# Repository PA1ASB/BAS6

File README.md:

# BAS6 - Remote controlled receive antenna switch for 6 beverage antennas

This project describes a 6-way receive antenna switch I built for a fellow radio amateur that allows to select one of six beverage wire antennas remotely and producing as little as possible noise around the connection to his receive amplifier. Using bi-stable relays makes it possible to completely disconnect power to the relays once an antenna has been selected. Switching is controlled by a small circuit, built in a tiny aluminium extrusion desktop enclosure, using two UP/DOWN tactile switches. Bi-colour LED’s on the from panel indicate the currently connected antenna and, when using the selection buttons, the next antenna to be switched on. Connection between the control station in the shack and the actual relay box requires 4 wires; using cheap UTP/FTP is therefore possible. The circuit should work over distances in excess of 200 meters as communication between the stations is done through two current loops (receive and transmit).

Control unit and relay box communicate “digitally” by sending some pulses to and fro, the number of which determine what the relaybox should actually do. After executing a command, the circuit measures which relay is actually switched on / off and reports this back to the control unit again as a series of pulses. If for whatever reason the reported switch state differs from what has been commanded, an error is indicated so that  the user knows there’s something wrong. This will prevent unnecessary walks from the shack to the antenna connections: what is  indicated on the control unit is the actual state.

The antennas are connected to the switch on the PVC junction box. I have made quite some effort in making the box and connections that are located outside of the box as watertight as possible but I guess that it is still advisable to make some additional protection to prevent direct exposure to the environment.

You can find the schematics of both units both as PDF and KiCAD v10 files as well as the C sources. I have also included BOM files for the PCB’s. There’s some additional hardware required such as stainless steel hardware for the antenna connections and switches to control the relays; these are not mentioned in these files. I have built the software in MPLAB IDE with the XC8 1.33 compiler. The C source should also compile in the newer MPLAB X IDE with the newer compiler versions but I believe that there are some minor syntax changes between the old and new versions which obviously need to be resolved. Google will be your friend for that, I guess.

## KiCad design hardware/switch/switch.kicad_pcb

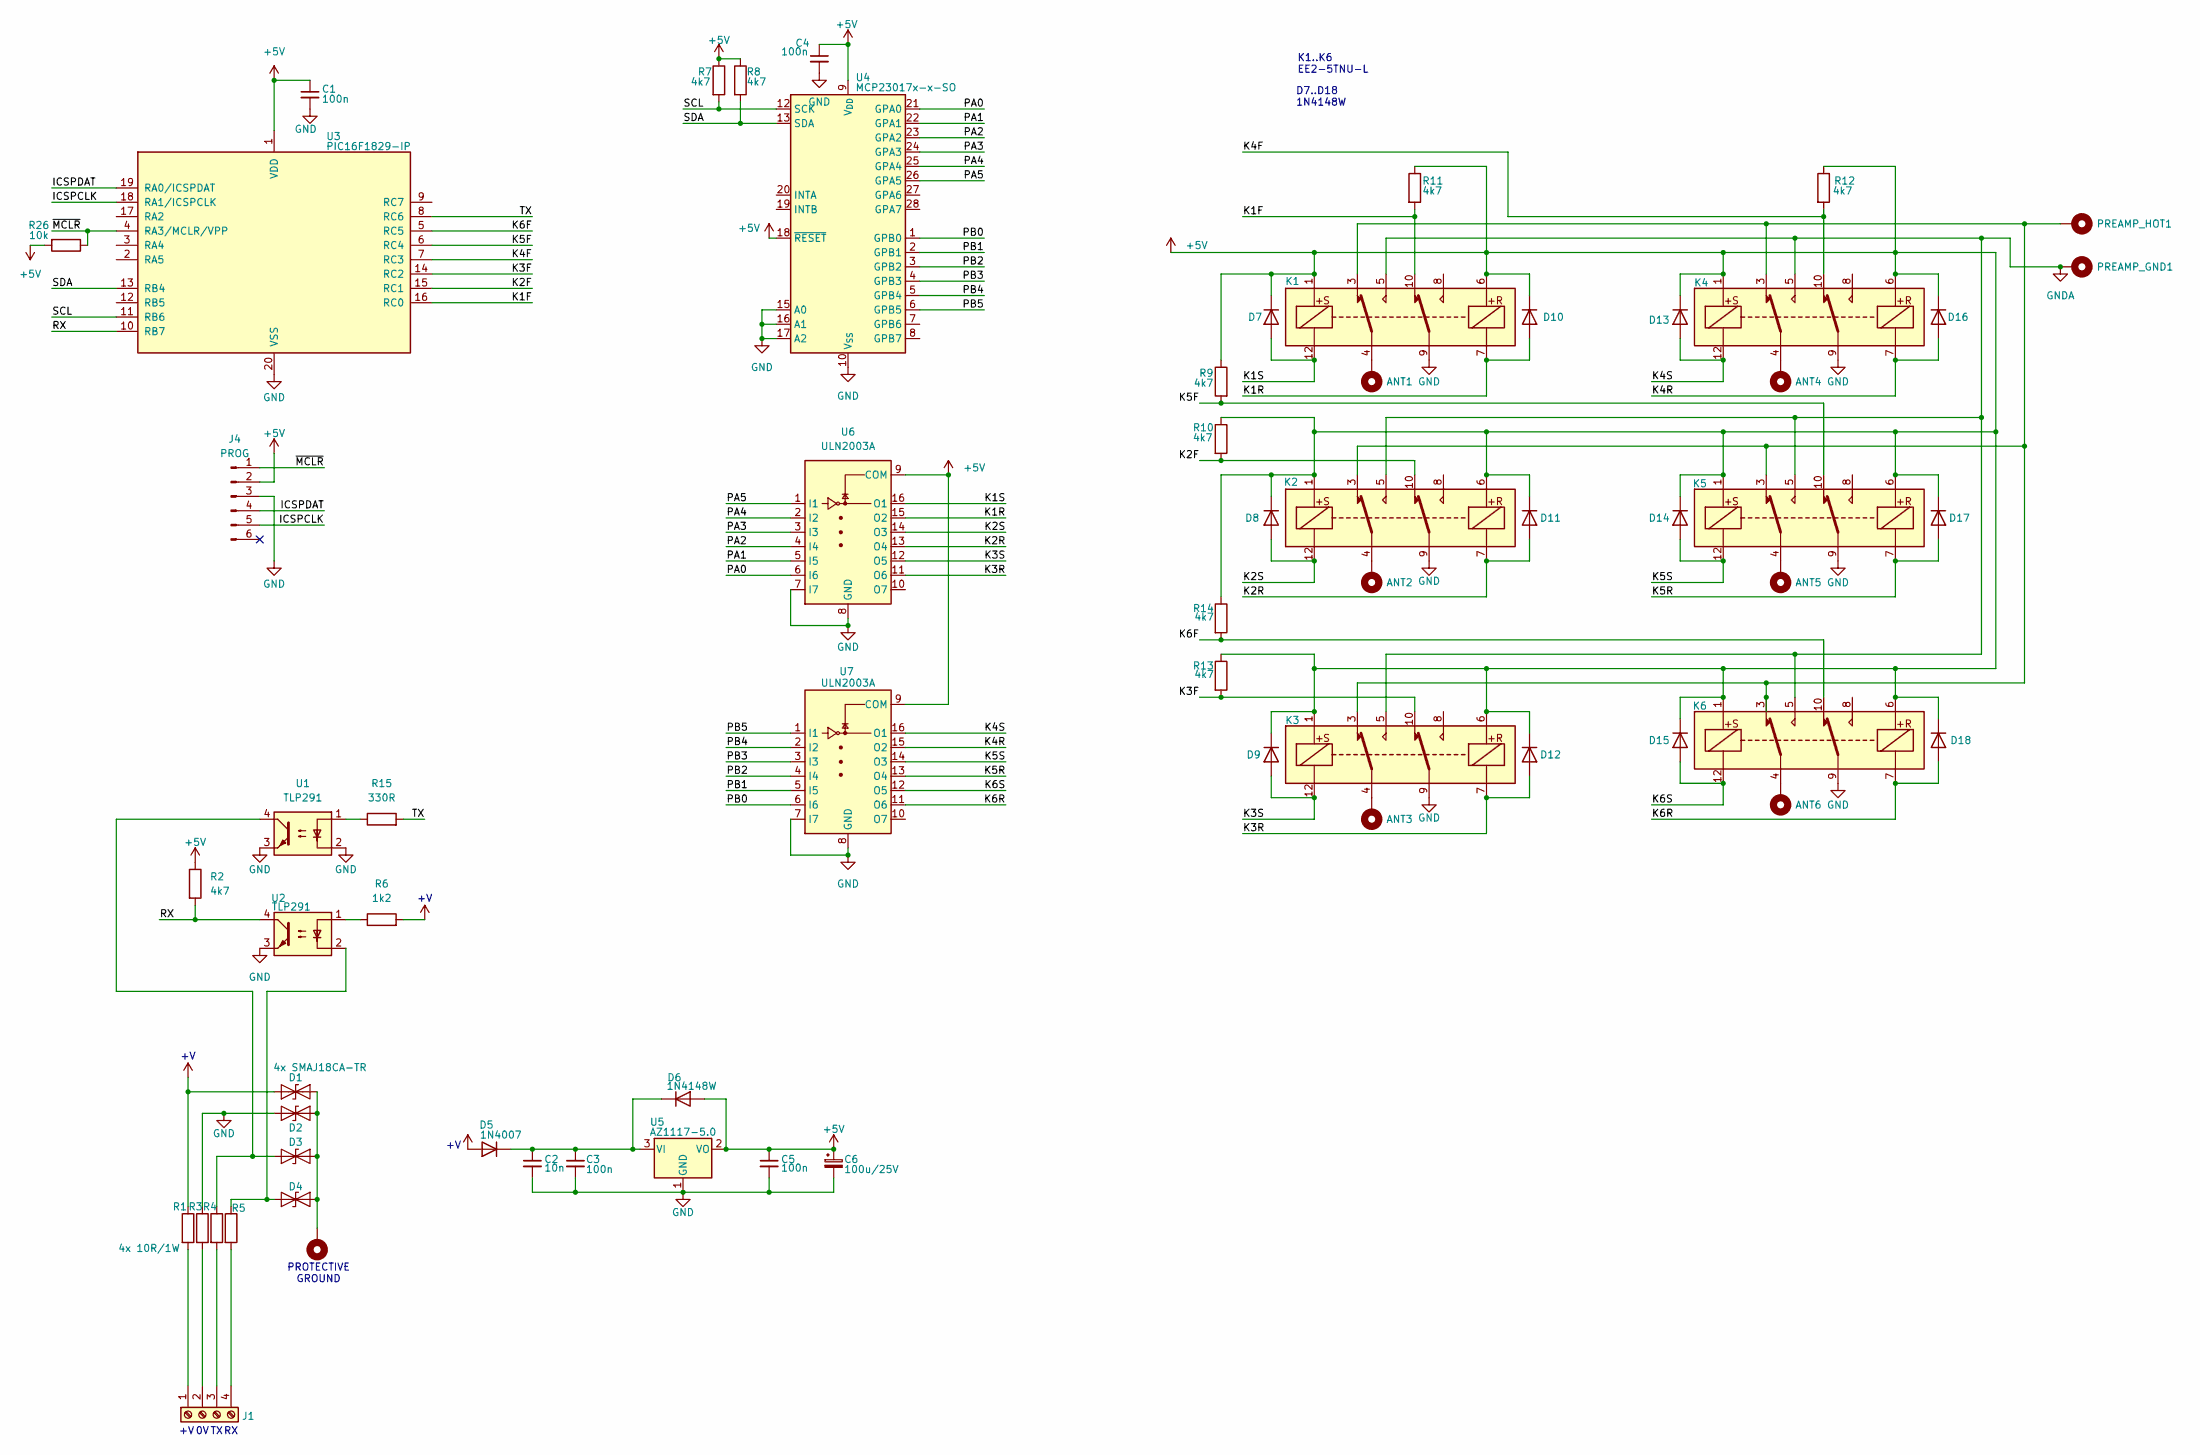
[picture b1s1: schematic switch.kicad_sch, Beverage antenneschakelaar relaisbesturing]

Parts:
ANT1, ANT2, ANT3, ANT4, ANT5, ANT6: MountingHole_Pad; MountingHole_4.3mm_M4_Pad_TopBottom
C1, C3, C4, C5: 100n; C_0805_2012Metric_Pad1.18x1.45mm_HandSolder
C2: 10n; C_0805_2012Metric_Pad1.18x1.45mm_HandSolder
C6: 100u/25V; CP_Elec_10x10
D1, D2, D3: SMAJ18CA-TR; D_SMA
D4: 4x SMAJ18CA-TR; D_SMA
D5: 1N4007; D_DO-41_SOD81_P10.16mm_Horizontal
D6, D7, D8, D9, D10, D11, D12, D13, D14, D15, D16, D17, D18: 1N4148W; D_SOD-123
GROUND1: MountingHole_Pad; MountingHole_5.3mm_M5_DIN965_Pad_TopBottom
J1: Screw_Terminal_01x04; TerminalBlock_Phoenix_MPT-0,5-4-2.54_1x04_P2.54mm_Horizontal
J4: PROG; PinHeader_1x06_P2.54mm_Vertical
K1, K2, K3, K4, K5, K6: EE2-5TNU-L; Relay_DPDT_Kemet_EE2_NU_DoubleCoil
PREAMP_GND1: MountingHole_Pad; MountingHole_4.3mm_M4_Pad_TopBottom
PREAMP_HOT1: MountingHole_Pad; MountingHole_4.3mm_M4_Pad_TopBottom
R1, R4, R5: 10R/1W; R_1206_3216Metric_Pad1.30x1.75mm_HandSolder
R2, R7, R8, R9, R10, R11, R12, R13, R14: 4k7; R_0805_2012Metric_Pad1.20x1.40mm_HandSolder
R3: 4x 10R/1W; R_1206_3216Metric_Pad1.30x1.75mm_HandSolder
R6: 1k2; R_0805_2012Metric_Pad1.20x1.40mm_HandSolder
R15: 330R; R_0805_2012Metric_Pad1.20x1.40mm_HandSolder
R26: 10k; R_0805_2012Metric_Pad1.20x1.40mm_HandSolder
U1, U2: TLP291; SOIC-4_4.55x2.6mm_P1.27mm
U3: PIC16F1829-IP; SOIC-20W_7.5x12.8mm_P1.27mm
U4: MCP23017x-x-SO; SOIC-28W_7.5x17.9mm_P1.27mm
U5: AZ1117-5.0; SOT-223-3_TabPin2
U6, U7: ULN2003A; SOIC-16_3.9x9.9mm_P1.27mm

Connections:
+5V: C1.1, C4.1, C5.1, C6.1, D6.2 (A), D7.1 (K), D8.1 (K), D9.1 (K), D10.1 (K), D11.1 (K), D12.1 (K), D13.1 (K), D14.1 (K), D15.1 (K), D16.1 (K), D17.1 (K), D18.1 (K), J4.2, K1.1, K1.6, K2.1, K2.6, K3.1, K3.6, K4.1, K4.6, K5.1, K5.6, K6.1, K6.6, R2.1, R7.1, R8.1, R9.1, R10.1, R11.1, R12.1, R13.1, R14.1, R26.2, U3.1 (VDD), U4.9 (V_{DD}), U4.18 (~RESET), U5.2 (VO), U6.9 (COM), U7.9 (COM)
+12V: D1.1 (A1), D5.2 (A), R1.1, R6.2
/ICSPCLK: J4.5, U3.18 (RA1/ICSPCLK)
/ICSPDAT: J4.4, U3.19 (RA0/ICSPDAT)
/K1F: K1.10, R11.2, U3.16 (RC0)
/K1R: D10.2 (A), K1.7, U6.15 (O2)
/K1S: D7.2 (A), K1.12, U6.16 (O1)
/K2F: K2.10, R10.2, U3.15 (RC1)
/K2R: D11.2 (A), K2.7, U6.13 (O4)
/K2S: D8.2 (A), K2.12, U6.14 (O3)
/K3F: K3.10, R13.2, U3.14 (RC2)
/K3R: D12.2 (A), K3.7, U6.11 (O6)
/K3S: D9.2 (A), K3.12, U6.12 (O5)
/K4F: K4.10, R12.2, U3.7 (RC3)
/K4R: D16.2 (A), K4.7, U7.15 (O2)
/K4S: D13.2 (A), K4.12, U7.16 (O1)
/K5F: K5.10, R9.2, U3.6 (RC4)
/K5R: D17.2 (A), K5.7, U7.13 (O4)
/K5S: D14.2 (A), K5.12, U7.14 (O3)
/K6F: K6.10, R14.2, U3.5 (RC5)
/K6R: D18.2 (A), K6.7, U7.11 (O6)
/K6S: D15.2 (A), K6.12, U7.12 (O5)
/PA0: U4.21 (GPA0), U6.6 (I6)
/PA1: U4.22 (GPA1), U6.5 (I5)
/PA2: U4.23 (GPA2), U6.4 (I4)
/PA3: U4.24 (GPA3), U6.3 (I3)
/PA4: U4.25 (GPA4), U6.2 (I2)
/PA5: U4.26 (GPA5), U6.1 (I1)
/PB0: U4.1 (GPB0), U7.6 (I6)
/PB1: U4.2 (GPB1), U7.5 (I5)
/PB2: U4.3 (GPB2), U7.4 (I4)
/PB3: U4.4 (GPB3), U7.3 (I3)
/PB4: U4.5 (GPB4), U7.2 (I2)
/PB5: U4.6 (GPB5), U7.1 (I1)
/RX: R2.2, U2.4, U3.10 (RB7)
/SCL: R7.2, U3.11 (RB6), U4.12 (SCK)
/SDA: R8.2, U3.13 (RB4), U4.13 (SDA)
/TX: R15.2, U3.8 (RC6)
/~MCLR: J4.1, R26.1, U3.4 (RA3/MCLR/VPP)
GND: C1.2, C2.2, C3.2, C4.2, C5.2, C6.2, D2.1 (A1), J4.3, K1.9, K2.9, K3.9, K4.9, K5.9, K6.9, R3.1, U1.2, U1.3, U2.3, U3.20 (VSS), U4.10 (V_{SS}), U4.15 (A0), U4.16 (A1), U4.17 (A2), U5.1 (GND), U6.7 (I7), U6.8 (GND), U7.7 (I7), U7.8 (GND)
GNDA: K1.5, K2.5, K3.5, K4.5, K5.5, K6.5, PREAMP_GND1.1 (1_1)
unnamed: ANT1.1 (1_1), K1.4
unnamed: ANT2.1 (1_1), K2.4
unnamed: ANT3.1 (1_1), K3.4
unnamed: ANT4.1 (1_1), K4.4
unnamed: ANT5.1 (1_1), K5.4
unnamed: ANT6.1 (1_1), K6.4
unnamed: D1.2 (A2), D2.2 (A2), D3.2 (A2), D4.2 (A2), GROUND1.1 (1_1)
unnamed: D3.1 (A1), R4.1, U1.4
unnamed: D4.1 (A1), R5.1, U2.2
unnamed: C2.1, C3.1, D5.1 (K), D6.1 (K), U5.3 (VI)
unnamed: J1.1, R1.2
unnamed: J1.2, R3.2
unnamed: J1.3, R4.2
unnamed: J1.4, R5.2
unnamed: K1.3, K2.3, K3.3, K4.3, K5.3, K6.3, PREAMP_HOT1.1 (1_1)
unnamed: R6.1, U2.1
unnamed: R15.1, U1.1

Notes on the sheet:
K1..K6 EE2-5TNU-L
D7..D18 1N4148W
PROTECTIVE GROUND

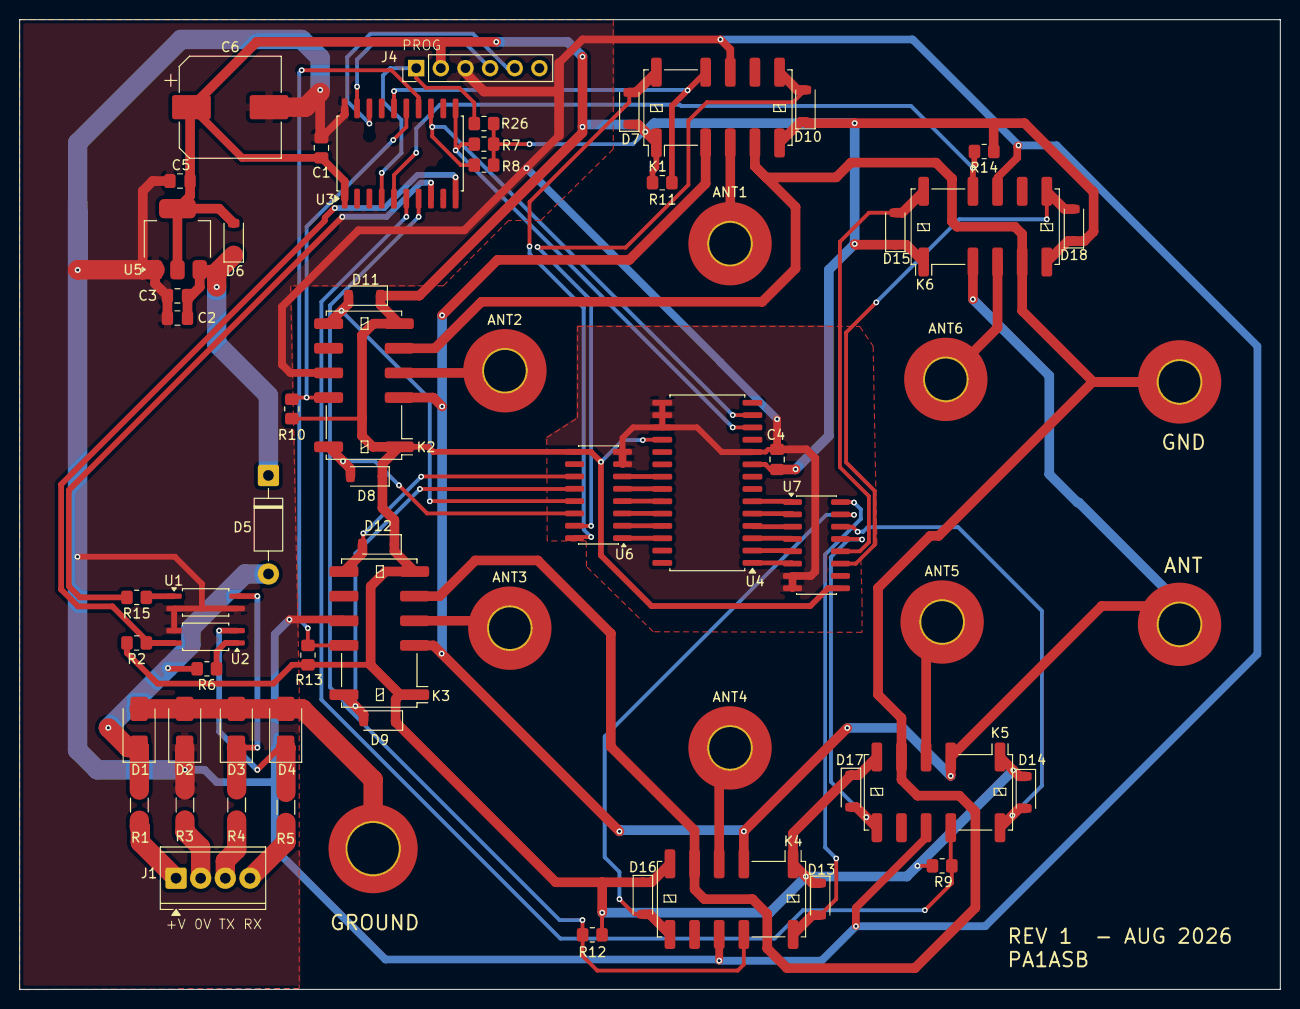
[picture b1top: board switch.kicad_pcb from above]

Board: 2 copper layers, 130.0 x 100.0 mm, 64 parts (0 on the bottom side), 58 nets.

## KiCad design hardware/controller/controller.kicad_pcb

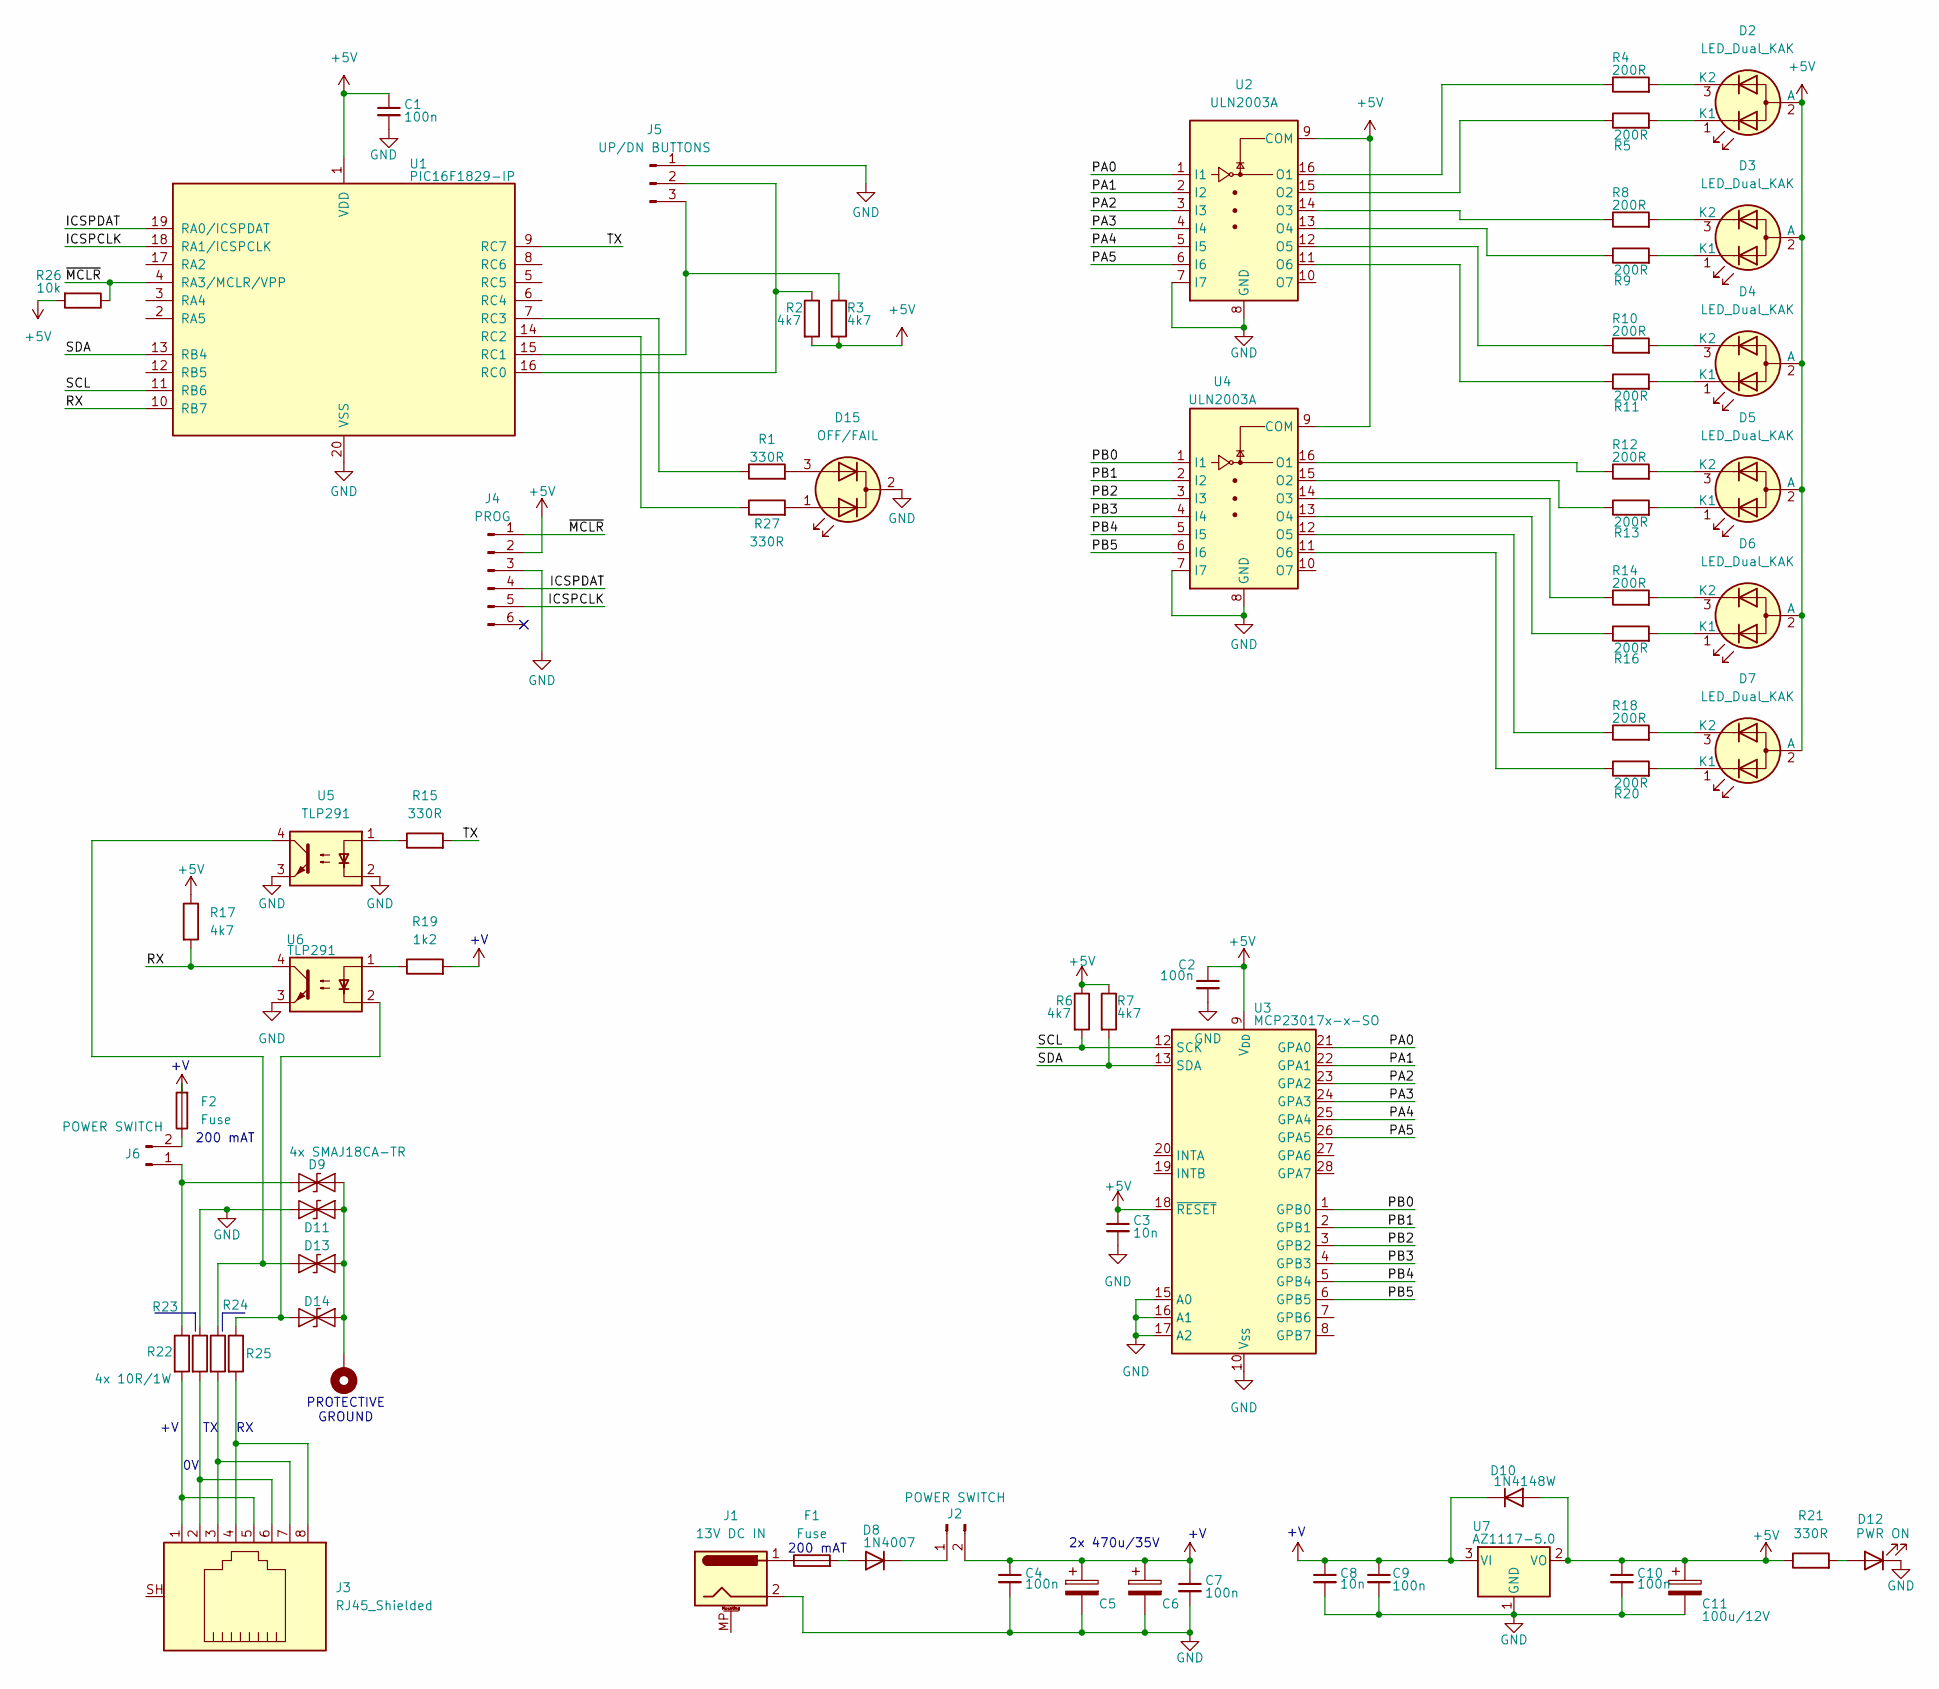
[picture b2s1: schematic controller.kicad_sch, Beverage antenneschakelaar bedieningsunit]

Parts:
C1, C2, C4, C7, C9, C10: 100n; C_0805_2012Metric_Pad1.18x1.45mm_HandSolder
C3, C8: 10n; C_0805_2012Metric_Pad1.18x1.45mm_HandSolder
C5, C6: 470u/35V; CP_Radial_D8.0mm_P3.50mm
C11: 100u/12V; CP_Radial_D8.0mm_P3.50mm
D2, D3, D4, D5, D6, D7: LED_Dual_KAK; LED_D5.0mm-3_Horizontal_O3.81mm_Z3.0mm
D8: 1N4007; D_DO-41_SOD81_P10.16mm_Horizontal
D9, D11, D13: SMAJ18CA-TR; D_SMA
D10: 1N4148W; D_SOD-123
D12: PWR ON; LED_D5.0mm_Horizontal_O6.35mm_Z15.0mm
D14: 4x SMAJ18CA-TR; D_SMA
D15: OFF/FAIL; LED_D5.0mm-3_Horizontal_O3.81mm_Z3.0mm
F1, F2: Fuse; Fuseholder_Cylinder-5x20mm_Stelvio-Kontek_PTF78_Horizontal_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
GROUND1: MountingHole_Pad; MountingHole_2.2mm_M2_DIN965_Pad_TopBottom
J1: 13V DC IN; BarrelJack_GCT_DCJ200-10-A_Horizontal
J2, J6: POWER SWITCH; PinHeader_1x02_P2.54mm_Vertical
J3: RJ45_Shielded; RJ45_Amphenol_RJHSE5380
J4: PROG; PinHeader_1x06_P2.54mm_Vertical
J5: UP/DN BUTTONS; PinHeader_1x03_P2.54mm_Vertical
R1, R15, R21, R27: 330R; R_0805_2012Metric_Pad1.20x1.40mm_HandSolder
R2, R3, R6, R7, R17: 4k7; R_0805_2012Metric_Pad1.20x1.40mm_HandSolder
R4, R5, R8, R9, R10, R11, R12, R13, R14, R16, R18, R20: 200R; R_0805_2012Metric_Pad1.20x1.40mm_HandSolder
R19: 1k2; R_0805_2012Metric_Pad1.20x1.40mm_HandSolder
R22, R24, R25: 10R/1W; R_1206_3216Metric_Pad1.30x1.75mm_HandSolder
R23: 4x 10R/1W; R_1206_3216Metric_Pad1.30x1.75mm_HandSolder
R26: 10k; R_0805_2012Metric_Pad1.20x1.40mm_HandSolder
U1: PIC16F1829-IP; SOIC-20W_7.5x12.8mm_P1.27mm
U2, U4: ULN2003A; SOIC-16_3.9x9.9mm_P1.27mm
U3: MCP23017x-x-SO; SOIC-28W_7.5x17.9mm_P1.27mm
U5, U6: TLP291; SOIC-4_4.55x2.6mm_P1.27mm
U7: AZ1117-5.0; SOT-223-3_TabPin2

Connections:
+5V: C1.1, C2.1, C3.1, C10.1, C11.1, D2.2 (A), D3.2 (A), D4.2 (A), D5.2 (A), D6.2 (A), D7.2 (A), D10.2 (A), J4.2, R2.2, R3.2, R6.1, R7.1, R17.1, R21.1, R26.2, U1.1 (VDD), U2.9 (COM), U3.9 (V_{DD}), U3.18 (~RESET), U4.9 (COM), U7.2 (VO)
+12V: C4.1, C5.1, C6.1, C7.1, C8.1, C9.1, D10.1 (K), F2.2, J2.2, R19.2, U7.3 (VI)
/ICSPCLK: J4.5, U1.18 (RA1/ICSPCLK)
/ICSPDAT: J4.4, U1.19 (RA0/ICSPDAT)
/PA0: U2.1 (I1), U3.21 (GPA0)
/PA1: U2.2 (I2), U3.22 (GPA1)
/PA2: U2.3 (I3), U3.23 (GPA2)
/PA3: U2.4 (I4), U3.24 (GPA3)
/PA4: U2.5 (I5), U3.25 (GPA4)
/PA5: U2.6 (I6), U3.26 (GPA5)
/PB0: U3.1 (GPB0), U4.1 (I1)
/PB1: U3.2 (GPB1), U4.2 (I2)
/PB2: U3.3 (GPB2), U4.3 (I3)
/PB3: U3.4 (GPB3), U4.4 (I4)
/PB4: U3.5 (GPB4), U4.5 (I5)
/PB5: U3.6 (GPB5), U4.6 (I6)
/RX: R17.2, U1.10 (RB7), U6.4
/SCL: R6.2, U1.11 (RB6), U3.12 (SCK)
/SDA: R7.2, U1.13 (RB4), U3.13 (SDA)
/TX: R15.2, U1.9 (RC7)
/~MCLR: J4.1, R26.1, U1.4 (RA3/MCLR/VPP)
GND: C1.2, C2.2, C3.2, C4.2, C5.2, C6.2, C7.2, C8.2, C9.2, C10.2, C11.2, D11.1 (A1), D12.1 (K), D15.2 (K), J1.2, J4.3, J5.1, R23.1, U1.20 (VSS), U2.7 (I7), U2.8 (GND), U3.10 (V_{SS}), U3.15 (A0), U3.16 (A1), U3.17 (A2), U4.7 (I7), U4.8 (GND), U5.2, U5.3, U6.3, U7.1 (GND)
unnamed: D2.1 (K1), R5.2
unnamed: D2.3 (K2), R4.2
unnamed: D3.1 (K1), R9.2
unnamed: D3.3 (K2), R8.2
unnamed: D4.1 (K1), R11.2
unnamed: D4.3 (K2), R10.2
unnamed: D5.1 (K1), R13.2
unnamed: D5.3 (K2), R12.2
unnamed: D6.1 (K1), R16.2
unnamed: D6.3 (K2), R14.2
unnamed: D7.1 (K1), R20.2
unnamed: D7.3 (K2), R18.2
unnamed: D8.2 (A), F1.2
unnamed: D8.1 (K), J2.1
unnamed: D9.1 (A1), J6.1, R22.1
unnamed: D9.2 (A2), D11.2 (A2), D13.2 (A2), D14.2 (A2), GROUND1.1 (1_1)
unnamed: D12.2 (A), R21.2
unnamed: D13.1 (A1), R24.1, U5.4
unnamed: D14.1 (A1), R25.1, U6.2
unnamed: D15.1 (A1), R27.2
unnamed: D15.3 (A2), R1.2
unnamed: F1.1, J1.1
unnamed: J3.1, J3.5, R22.2
unnamed: J3.2, J3.6, R23.2
unnamed: J3.3, J3.7, R24.2
unnamed: J3.4, J3.8, R25.2
unnamed: J5.2, R2.1, U1.16 (RC0)
unnamed: J5.3, R3.1, U1.15 (RC1)
unnamed: F2.1, J6.2
unnamed: R15.1, U5.1
unnamed: R19.1, U6.1
unnamed: R27.1, U1.14 (RC2)
unnamed: R1.1, U1.7 (RC3)
unnamed: R4.1, U2.16 (O1)
unnamed: R5.1, U2.15 (O2)
unnamed: R8.1, U2.14 (O3)
unnamed: R9.1, U2.13 (O4)
unnamed: R10.1, U2.12 (O5)
unnamed: R11.1, U2.11 (O6)
unnamed: R12.1, U4.16 (O1)
unnamed: R13.1, U4.15 (O2)
unnamed: R14.1, U4.14 (O3)
unnamed: R16.1, U4.13 (O4)
unnamed: R18.1, U4.12 (O5)
unnamed: R20.1, U4.11 (O6)

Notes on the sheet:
PROTECTIVE GROUND
2x 470u/35V
200 mAT

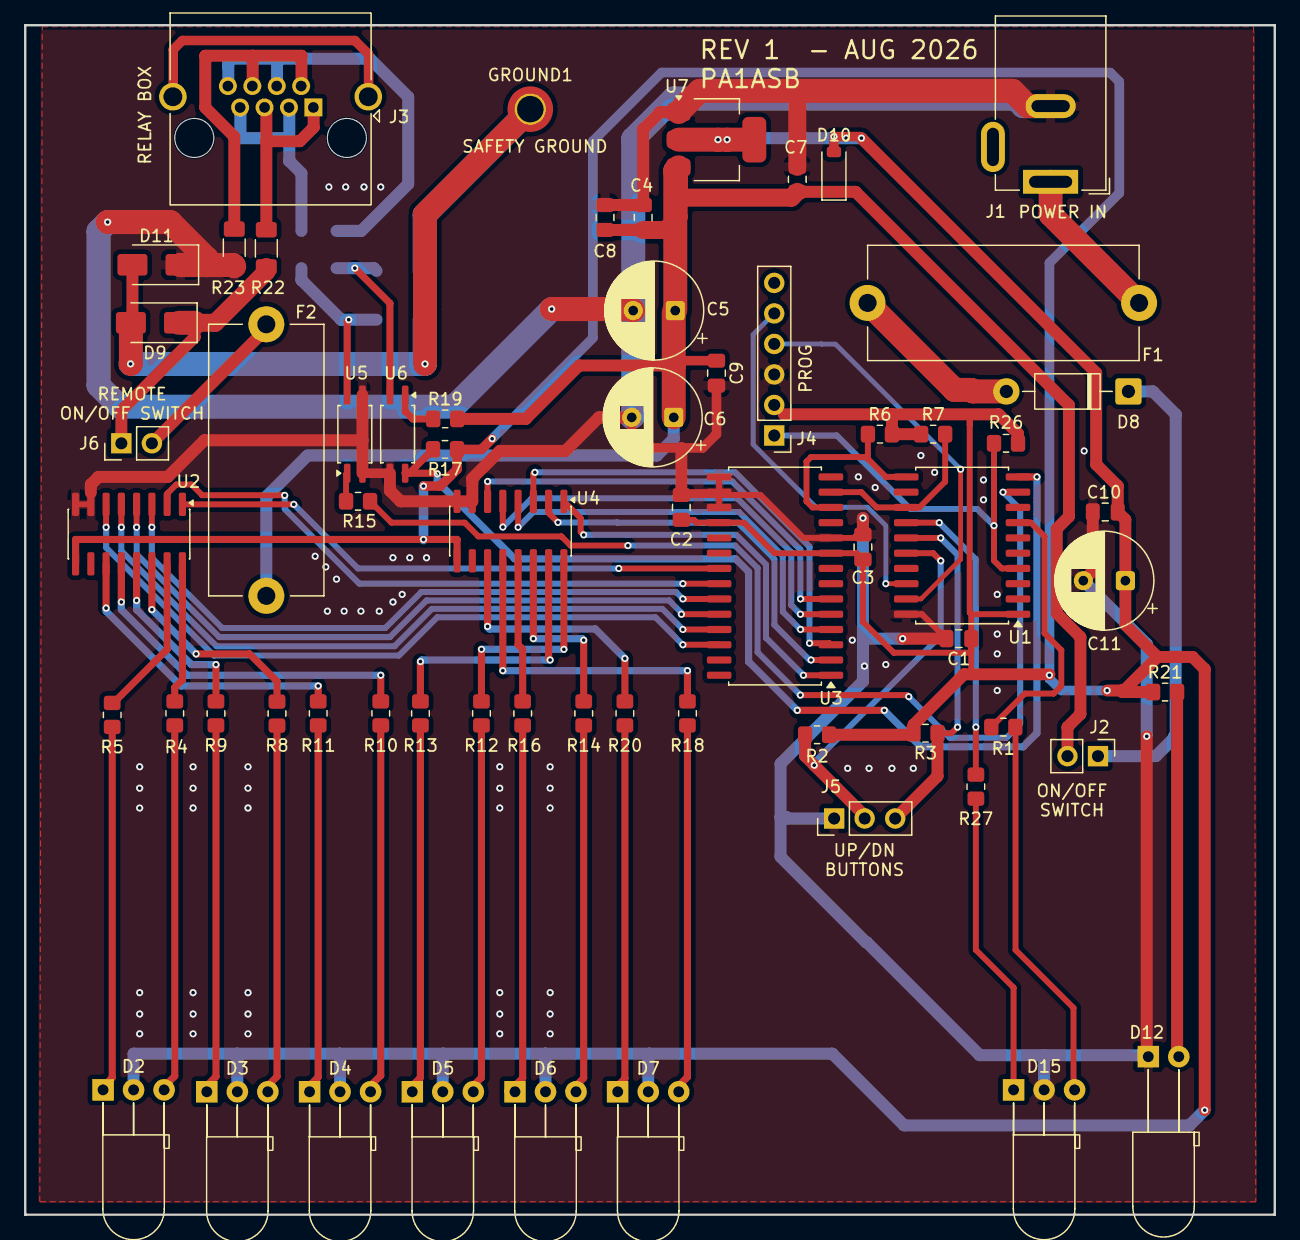
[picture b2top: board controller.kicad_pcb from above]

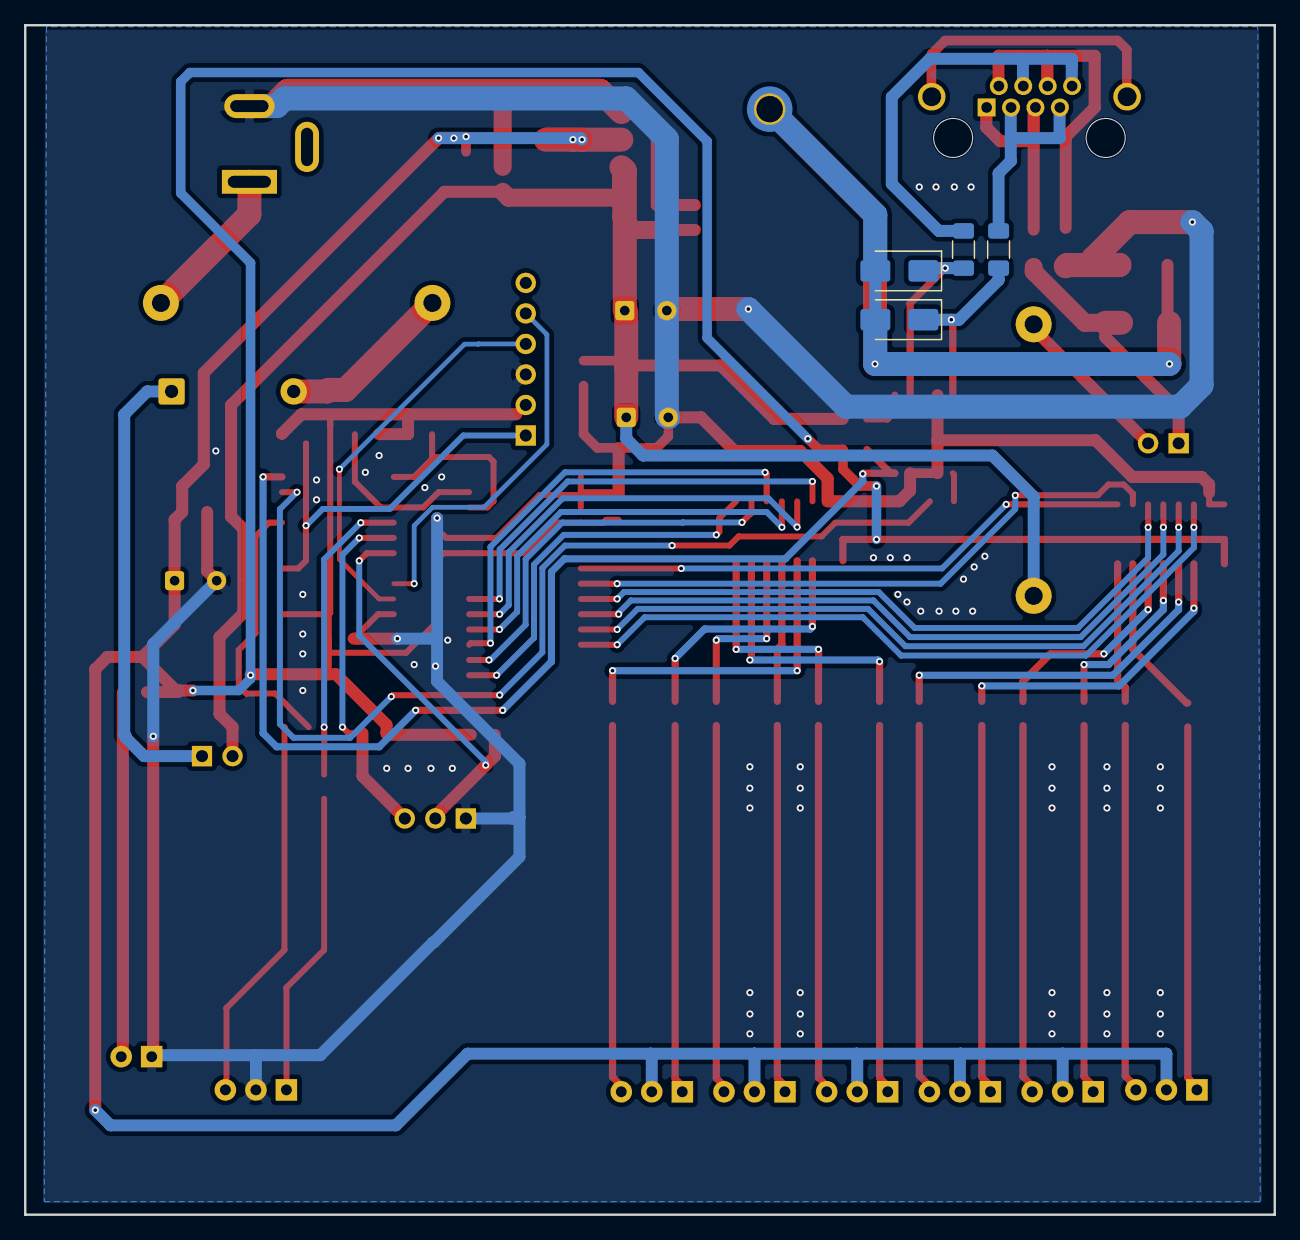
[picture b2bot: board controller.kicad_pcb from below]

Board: 2 copper layers, 104.0 x 99.0 mm, 68 parts (4 on the bottom side), 67 nets.

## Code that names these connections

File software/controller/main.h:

#ifndef MAIN_H
#define	MAIN_H

#include <xc.h>
#include <stdint.h>
#include <stdbool.h>
#include "interrupt.h"
#include "i2c.h"
#include "mcp23017.h"
#include "system.h"

// Configuration Bits (PIC16F1829)
#pragma config FOSC = INTOSC    // Internal oscillator
#pragma config WDTE = ON        // Watchdog Timer ON 
#pragma config PWRTE = ON       // Power-up Timer ON
#pragma config MCLRE = ON       // MCLR pin active
#pragma config CP = OFF         // Code Protection OFF
#pragma config BOREN = ON       // Brown-out Reset ON
#pragma config CLKOUTEN = OFF   // Clock Out function OFF
#pragma config IESO = OFF       // Internal/External Switchover OFF
#pragma config FCMEN = OFF      // Fail-Safe Clock Monitor OFF

#define _XTAL_FREQ 16000000     // 16 MHz; required for delay macros

// I/O pin definitions
#define BTN_UP      PORTCbits.RC0
#define BTN_DN      PORTCbits.RC1
#define LED_RED     PORTCbits.RC2
#define LED_GREEN   PORTCbits.RC3
#define RX_PIN      PORTBbits.RB7
#define TX_PIN      LATCbits.LATC7

// MCP23017 I2C Address, A0, A1, A2 tied to GND
#define MCP23017_ADDR 0x40

// State machine definitions
typedef enum {
    STATE_START,
	STATE_REQ_INFO,
    STATE_IDLE,
    STATE_SEND,
    STATE_RECEIVE,
    STATE_ERROR
} MasterState_t;

// Some timing stuff
#define START_PULSE_TIMEOUT		 ((uint16_t)1500)
#define COUNT_SAMPLE_TIME_WINDOW ((uint16_t)300)
#define START_PULSE_HIGH_TIME	 ((uint8_t)15)
#define START_PULSE_LOW_TIME	 ((uint8_t)5)
#define	COUNTER_PULSE_HIGH_TIME	 ((uint8_t)3)
#define	COUNTER_PULSE_LOW_TIME	 ((uint8_t)3)

// Globals
MasterState_t currentState = STATE_START;
uint8_t current_antenna = 0;   // 1..6 = antenna 1..6, 7 = all OFF, 0 = unknown
uint8_t selected_antenna = 1;  // Antenna selected by operator

void DisplayAntennaSelection(uint8_t active, uint8_t selected);
void Set_Status_LED(uint8_t color); // 0=OFF, 1=GREEN, 2=RED, 3=ORANGE
bool Send_Frame(uint8_t data_mask);

// LED color definitions
#define COLOR_OFF    0
#define COLOR_GREEN  1
#define COLOR_RED    2
#define COLOR_ORANGE 3

#endif
